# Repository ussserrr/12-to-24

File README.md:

# 12-to-24

## Description
A step-up (also referred as boost) circuit is used to generate a higher voltage than the input voltage. The polarities are same as in the input. Output current is about 2-4A while ECE is about 80%.

Can be easily modified to produce 19V output for laptops (even on the fly using switch and resistor) in car.

## Notes
PCB was made firstly for the manual manufacturing so tracks widths are not meaningful and serve illustrative purposes. Remember that important critical parameters are closely related to conductors sizes.

Free space at the bottom is left for heat sinks as MOSFET and Schottky diodes are the most heated components.

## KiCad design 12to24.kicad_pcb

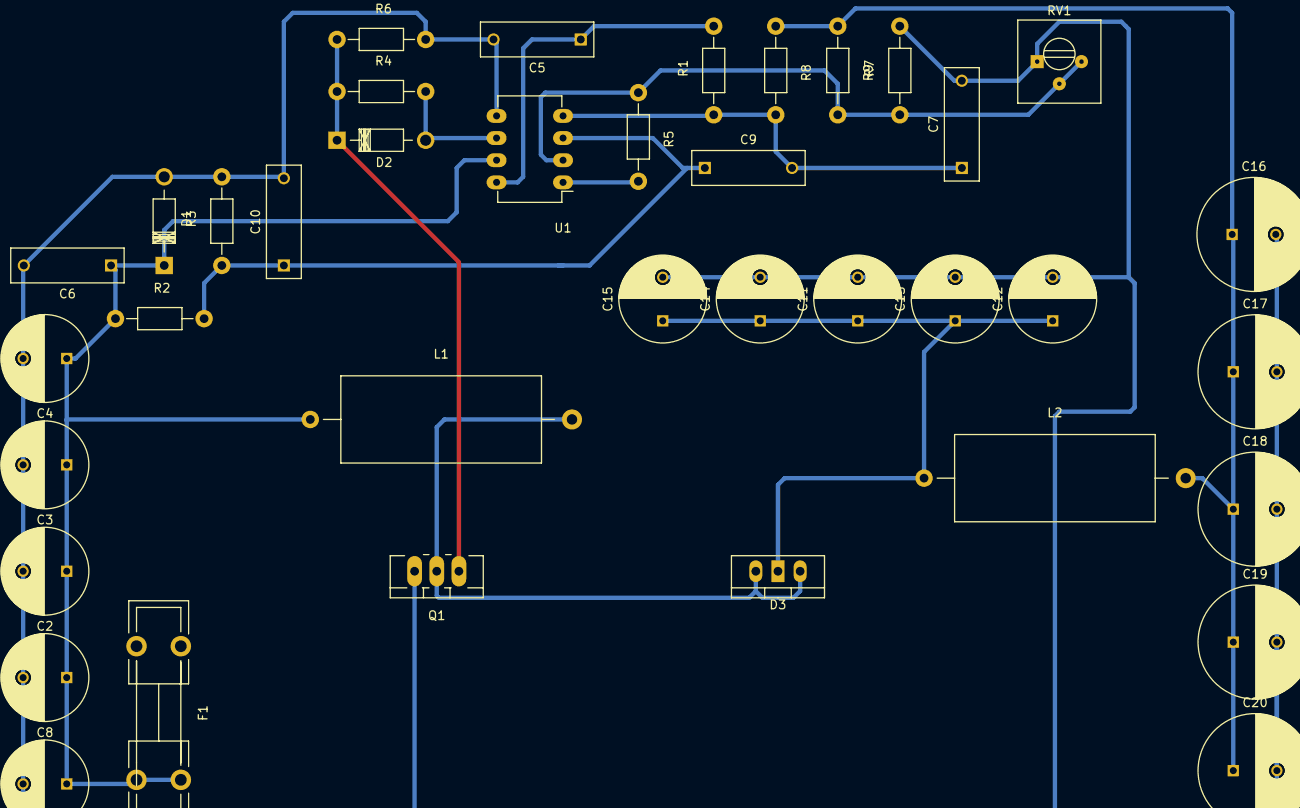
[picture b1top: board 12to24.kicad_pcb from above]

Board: 2 copper layers, 38 parts (0 on the bottom side), 12 nets.

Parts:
C1, C2, C3, C4, C8, C11, C12, C13, C14, C15: 470u; C_Radial_D10_L20_P5
C5, C6: 0.01u; C_Rect_L13_W4_P10
C7: 3.3n; C_Rect_L13_W4_P10
C9: C; C_Rect_L13_W4_P10
C10: 1n; C_Rect_L13_W4_P10
C16, C17, C18, C19, C20: 1000u; C_Radial_D13_L25_P5
D1, D2: D; Diode_DO-41_SOD81_Horizontal_RM10
D3: D_Schottky_x2_KCom_AKA; Diode_TO-220_Dual_CommonCathode_Vertical
F1: FUSE; Fuseholder5x20_horiz_open_lateral_Type-II
L1, L2: INDUCTOR; Choke_Horizontal_RM30mm
Q1: IRF540N; TO-220_Neutral123_Vertical_LargePads
R1: 3k3; Resistor_Horizontal_RM10mm
R2: 30k; Resistor_Horizontal_RM10mm
R3: 1k5; Resistor_Horizontal_RM10mm
R4: 10; Resistor_Horizontal_RM10mm
R5: 27k; Resistor_Horizontal_RM10mm
R6: 10k; Resistor_Horizontal_RM10mm
R7: 24k; Resistor_Horizontal_RM10mm
R8: 51k; Resistor_Horizontal_RM10mm
R9: 7k5; Resistor_Horizontal_RM10mm
RV1: POT; Potentiometer_Trimmer-Suntan-TSR-3386P
U1: UC3844BN; DIP-8_W7.62mm_LongPads

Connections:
+24V: C16.1, C17.1, C18.1, C19.1, C20.1, L2.2, R8.1, R9.1
Earth: C1.2, C2.2, C3.2, C4.2, C5.2, C6.2, C7.2, C8.2, C10.2, C11.2, C12.2, C13.2, C14.2, C15.2, C16.2, C17.2, C18.2, C19.2, C20.2, D1.2, Q1.3, R3.2, R6.2, R7.2, RV1.1, U1.5
unnamed: C1.1, C2.1, C3.1, C4.1, C6.1, C8.1, D1.1, F1.2, L1.1, R2.1, U1.7
unnamed: C5.1, R1.2, U1.8
unnamed: C7.1, C9.2, R1.1, R8.2, U1.4
unnamed: C9.1, C10.1, R2.2, R3.1, U1.3
unnamed: C11.1, C12.1, C13.1, C14.1, C15.1, D3.2, L2.1
unnamed: D2.1, Q1.1, R4.1, R6.1
unnamed: D2.2, R4.2, U1.6
unnamed: D3.1, D3.3, L1.2, Q1.2
unnamed: R5.1, R7.1, R9.2, RV1.2, RV1.3, U1.2
unnamed: R5.2, U1.1

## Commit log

2018-12-20 Add README, add preview images
